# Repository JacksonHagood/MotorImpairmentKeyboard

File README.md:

# MotorImpairmentKeyboard

# MIKey

Members:
- Jackson Hagood
- Andrew Imwalle
- Brittany Jenkins
- Connie Liu
- Abhishek More
- Max Smith

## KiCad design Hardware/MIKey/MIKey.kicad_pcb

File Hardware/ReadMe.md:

# Hardware

Gerber files for the footprint test, the matrix test, and the final Gerber files for the PCB request

Designing PCB

1. Follow install instructions at https://github.com/ncarandini/KiCad-RP-Pico to get the Raspberry Pi Pico footprint installed in KiCad
2. Ensure the Gateron Slim Footprint is also installed in KiCad
3. Use https://www.pcbway.com/blog/PCB_Design_Tutorial/How_to_Export_Gerber_and_Production_Files_in_KiCad.html to export files from KiCad to Gerber files used for printing PCB

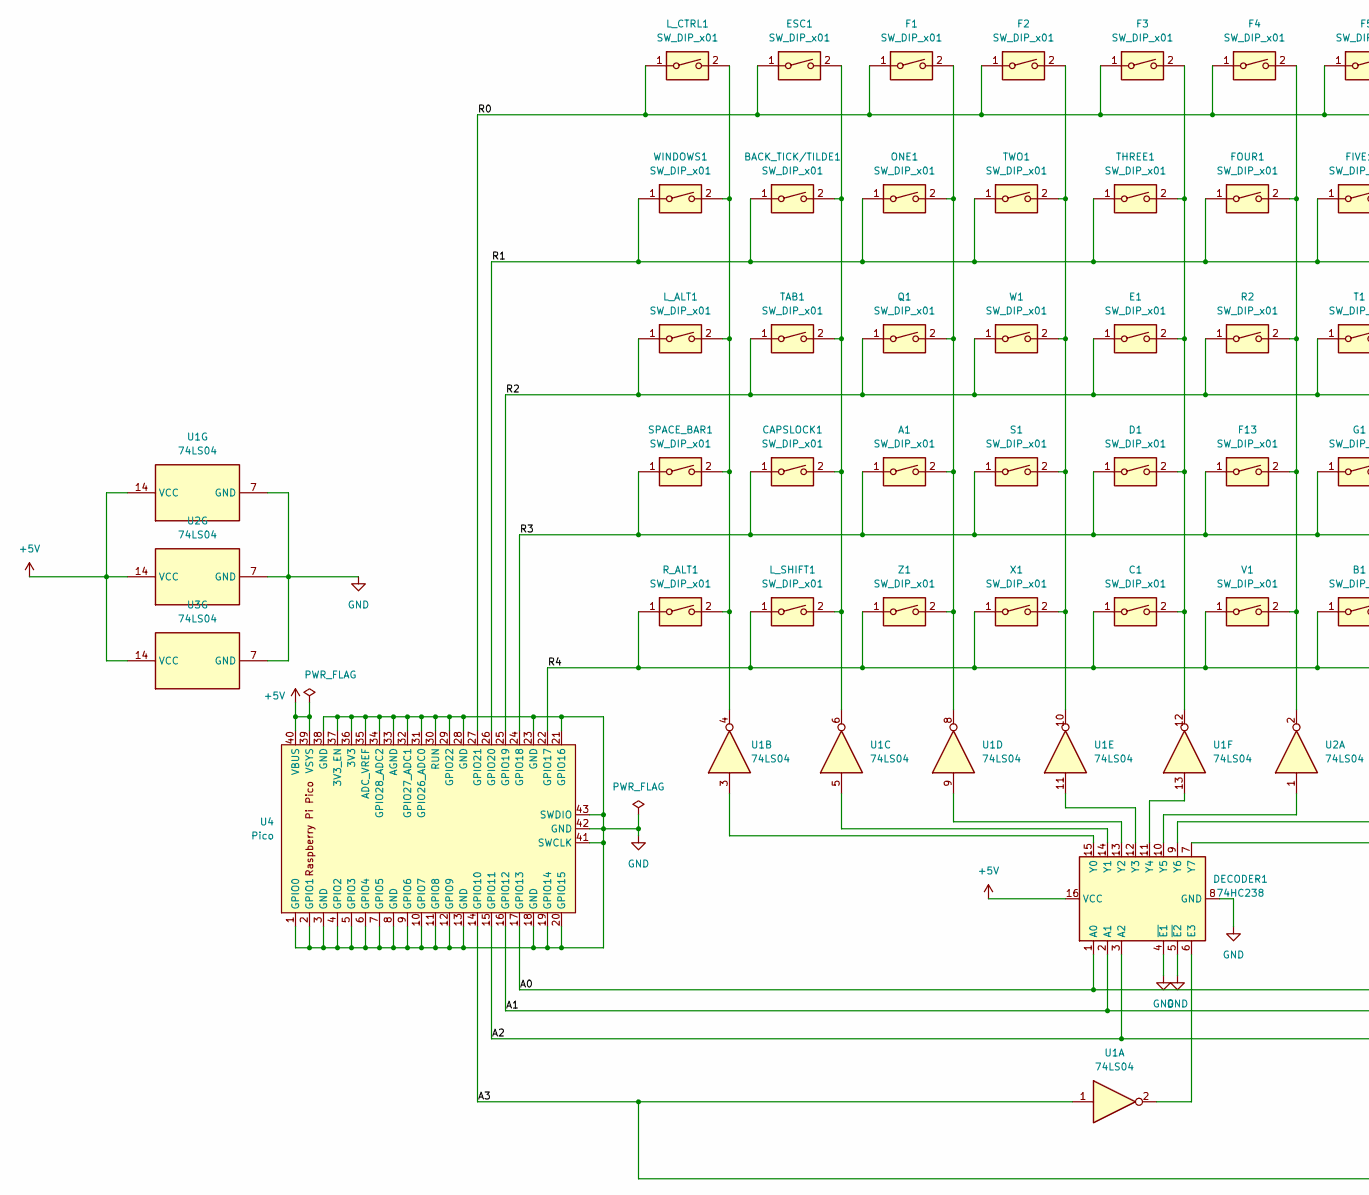
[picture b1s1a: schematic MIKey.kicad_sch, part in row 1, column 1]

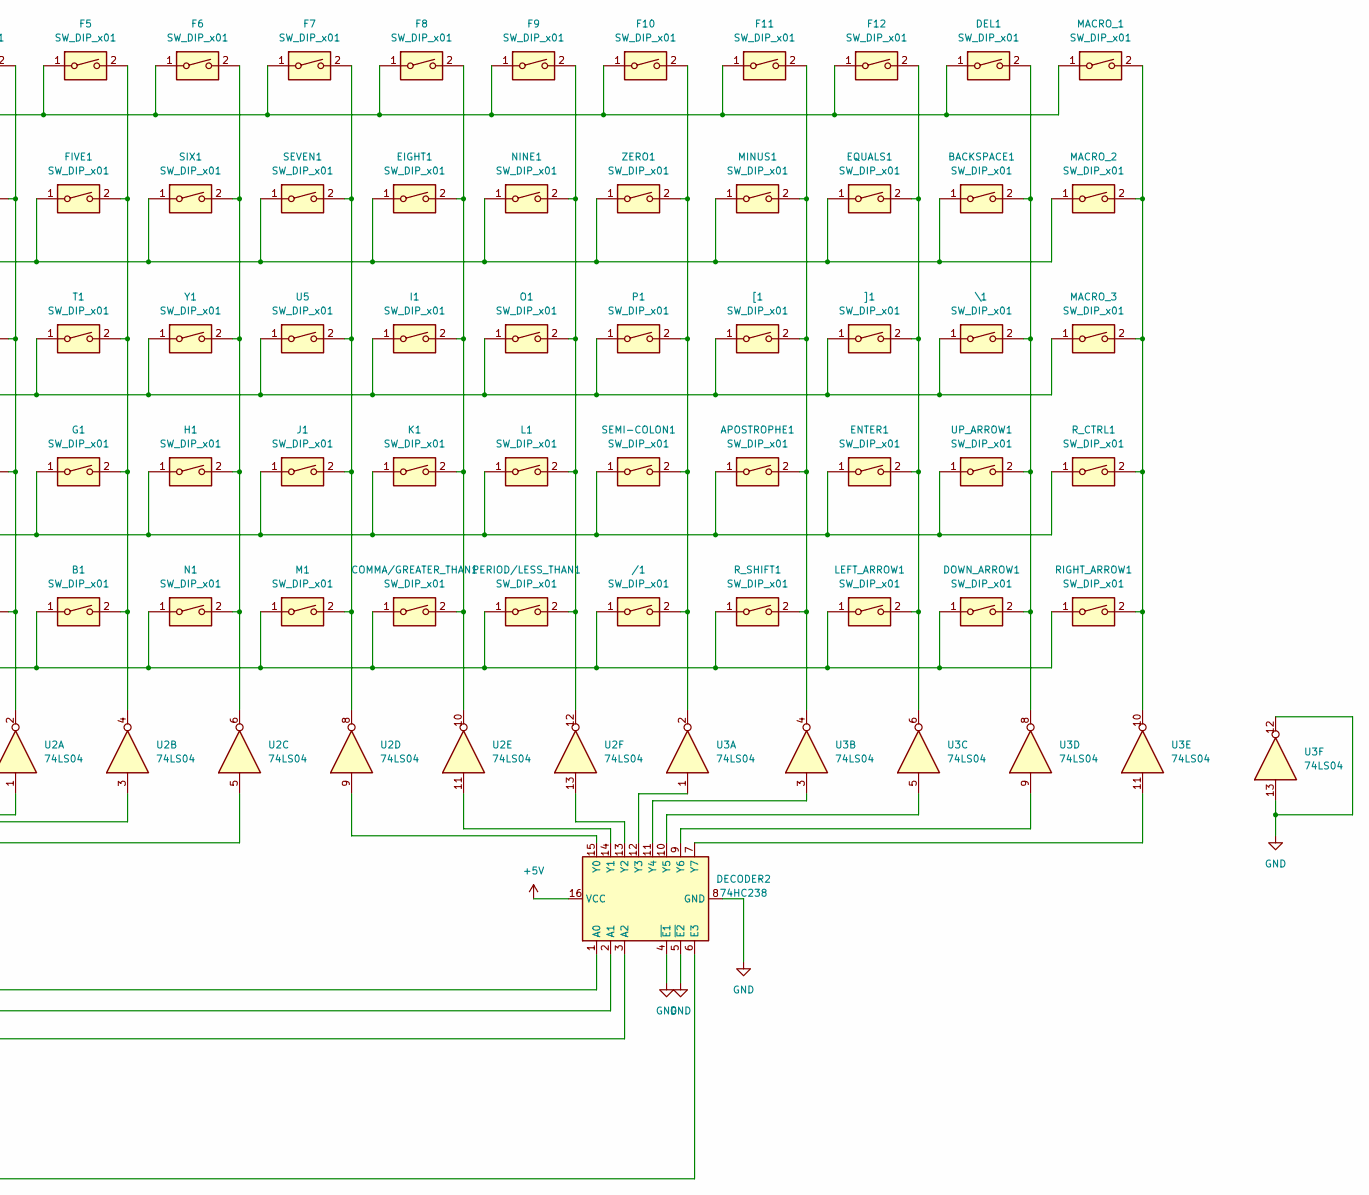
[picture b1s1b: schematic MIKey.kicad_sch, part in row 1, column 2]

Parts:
/1: SW_DIP_x01; gateron_slim
A1: SW_DIP_x01; gateron_slim
APOSTROPHE1: SW_DIP_x01; gateron_slim
B1: SW_DIP_x01; gateron_slim
BACKSPACE1: SW_DIP_x01; gateron_slim
BACK_TICK/TILDE1: SW_DIP_x01; gateron_slim
C1: SW_DIP_x01; gateron_slim
CAPSLOCK1: SW_DIP_x01; gateron_slim
COMMA/GREATER_THAN1: SW_DIP_x01; gateron_slim
D1: SW_DIP_x01; gateron_slim
DECODER1, DECODER2: 74HC238; DIP-16_W7.62mm
DEL1: SW_DIP_x01; gateron_slim
DOWN_ARROW1: SW_DIP_x01; gateron_slim
E1: SW_DIP_x01; gateron_slim
EIGHT1: SW_DIP_x01; gateron_slim
ENTER1: SW_DIP_x01; gateron_slim
EQUALS1: SW_DIP_x01; gateron_slim
ESC1: SW_DIP_x01; gateron_slim
F1, F2, F3, F4, F5, F6, F7, F8, F9, F10, F11, F12, F13: SW_DIP_x01; gateron_slim
FIVE1: SW_DIP_x01; gateron_slim
FOUR1: SW_DIP_x01; gateron_slim
G1: SW_DIP_x01; gateron_slim
H1: SW_DIP_x01; gateron_slim
I1: SW_DIP_x01; gateron_slim
J1: SW_DIP_x01; gateron_slim
K1: SW_DIP_x01; gateron_slim
L1: SW_DIP_x01; gateron_slim
LEFT_ARROW1: SW_DIP_x01; gateron_slim
L_ALT1: SW_DIP_x01; gateron_slim
L_CTRL1: SW_DIP_x01; gateron_slim
L_SHIFT1: SW_DIP_x01; gateron_slim
M1: SW_DIP_x01; gateron_slim
MACRO_1, MACRO_2, MACRO_3: SW_DIP_x01; gateron_slim
MINUS1: SW_DIP_x01; gateron_slim
N1: SW_DIP_x01; gateron_slim
NINE1: SW_DIP_x01; gateron_slim
O1: SW_DIP_x01; gateron_slim
ONE1: SW_DIP_x01; gateron_slim
P1: SW_DIP_x01; gateron_slim
PERIOD/LESS_THAN1: SW_DIP_x01; gateron_slim
Q1: SW_DIP_x01; gateron_slim
R2: SW_DIP_x01; gateron_slim
RIGHT_ARROW1: SW_DIP_x01; gateron_slim
R_ALT1: SW_DIP_x01; gateron_slim
R_CTRL1: SW_DIP_x01; gateron_slim
R_SHIFT1: SW_DIP_x01; gateron_slim
S1: SW_DIP_x01; gateron_slim
SEMI-COLON1: SW_DIP_x01; gateron_slim
SEVEN1: SW_DIP_x01; gateron_slim
SIX1: SW_DIP_x01; gateron_slim
SPACE_BAR1: SW_DIP_x01; gateron_slim
T1: SW_DIP_x01; gateron_slim
TAB1: SW_DIP_x01; gateron_slim
THREE1: SW_DIP_x01; gateron_slim
TWO1: SW_DIP_x01; gateron_slim
U1, U2, U3: 74LS04; DIP-14_W7.62mm
U4: Pico; RPi_Pico_SMD_TH
U5: SW_DIP_x01; gateron_slim
UP_ARROW1: SW_DIP_x01; gateron_slim
V1: SW_DIP_x01; gateron_slim
W1: SW_DIP_x01; gateron_slim
WINDOWS1: SW_DIP_x01; gateron_slim
X1: SW_DIP_x01; gateron_slim
Y1: SW_DIP_x01; gateron_slim
Z1: SW_DIP_x01; gateron_slim
ZERO1: SW_DIP_x01; gateron_slim
[1: SW_DIP_x01; gateron_slim
\1: SW_DIP_x01; gateron_slim
]1: SW_DIP_x01; gateron_slim

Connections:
+5V: DECODER1.16 (VCC), DECODER2.16 (VCC), U1.14 (VCC), U2.14 (VCC), U3.14 (VCC), U4.39 (VSYS), U4.40 (VBUS)
/A0: DECODER1.1 (A0), DECODER2.1 (A0), U4.17 (GPIO13)
/A1: DECODER1.2 (A1), DECODER2.2 (A1), U4.16 (GPIO12)
/A2: DECODER1.3 (A2), DECODER2.3 (A2), U4.15 (GPIO11)
/A3: DECODER2.6 (E3), U1.1, U4.14 (GPIO10)
/R0: DEL1.1, ESC1.1, F1.1, F2.1, F3.1, F4.1, F5.1, F6.1, F7.1, F8.1, F9.1, F10.1, F11.1, F12.1, L_CTRL1.1, MACRO_1.1, U4.27 (GPIO21)
/R1: BACKSPACE1.1, BACK_TICK/TILDE1.1, EIGHT1.1, EQUALS1.1, FIVE1.1, FOUR1.1, MACRO_2.1, MINUS1.1, NINE1.1, ONE1.1, SEVEN1.1, SIX1.1, THREE1.1, TWO1.1, U4.26 (GPIO20), WINDOWS1.1, ZERO1.1
/R2: E1.1, I1.1, L_ALT1.1, MACRO_3.1, O1.1, P1.1, Q1.1, R2.1, T1.1, TAB1.1, U4.25 (GPIO19), U5.1, W1.1, Y1.1, [1.1, \1.1, ]1.1
/R3: A1.1, APOSTROPHE1.1, CAPSLOCK1.1, D1.1, ENTER1.1, F13.1, G1.1, H1.1, J1.1, K1.1, L1.1, R_CTRL1.1, S1.1, SEMI-COLON1.1, SPACE_BAR1.1, U4.24 (GPIO18), UP_ARROW1.1
/R4: /1.1, B1.1, C1.1, COMMA/GREATER_THAN1.1, DOWN_ARROW1.1, LEFT_ARROW1.1, L_SHIFT1.1, M1.1, N1.1, PERIOD/LESS_THAN1.1, RIGHT_ARROW1.1, R_ALT1.1, R_SHIFT1.1, U4.22 (GPIO17), V1.1, X1.1, Z1.1; also elsewhere on the board
GND: DECODER1.4 (~E1), DECODER1.5 (~E2), DECODER1.8 (GND), DECODER2.4 (~E1), DECODER2.5 (~E2), DECODER2.8 (GND), U1.7 (GND), U2.7 (GND), U3.7 (GND), U3.12, U3.13, U4.1 (GPIO0), U4.2 (GPIO1), U4.3 (GND), U4.4 (GPIO2), U4.5 (GPIO3), U4.6 (GPIO4), U4.7 (GPIO5), U4.8 (GND), U4.9 (GPIO6), U4.10 (GPIO7), U4.11 (GPIO8), U4.12 (GPIO9), U4.13 (GND), U4.18 (GND), U4.19 (GPIO14), U4.20 (GPIO15), U4.21 (GPIO16), U4.23 (GND), U4.28 (GND), U4.29 (GPIO22), U4.30 (RUN), U4.31 (GPIO26_ADC0), U4.32 (GPIO27_ADC1), U4.33 (AGND), U4.34 (GPIO28_ADC2), U4.35 (ADC_VREF), U4.36 (3V3), U4.37 (3V3_EN), U4.38 (GND), U4.41 (SWCLK), U4.42 (GND), U4.43 (SWDIO)
unnamed: /1.2, F10.2, P1.2, SEMI-COLON1.2, U3.2, ZERO1.2
unnamed: A1.2, F1.2, ONE1.2, Q1.2, U1.8, Z1.2
unnamed: APOSTROPHE1.2, F11.2, MINUS1.2, R_SHIFT1.2, U3.4, [1.2
unnamed: B1.2, F5.2, FIVE1.2, G1.2, T1.2, U2.4
unnamed: BACKSPACE1.2, DEL1.2, DOWN_ARROW1.2, U3.8, UP_ARROW1.2, \1.2
unnamed: BACK_TICK/TILDE1.2, CAPSLOCK1.2, ESC1.2, L_SHIFT1.2, TAB1.2, U1.6
unnamed: C1.2, D1.2, E1.2, F3.2, THREE1.2, U1.12
unnamed 18: COMMA/GREATER_THAN1.2, EIGHT1.2, F8.2, I1.2, K1.2, U2.10; also elsewhere on the board
unnamed: DECODER1.6 (E3), U1.2
unnamed: DECODER1.7 (Y7), U2.5
unnamed: DECODER1.9 (Y6), U2.3
unnamed: DECODER1.10 (Y5), U2.1
unnamed: DECODER1.11 (Y4), U1.13
unnamed: DECODER1.12 (Y3), U1.11
unnamed: DECODER1.13 (Y2), U1.9
unnamed: DECODER1.14 (Y1), U1.5
unnamed: DECODER1.15 (Y0), U1.3
unnamed: DECODER2.7 (Y7), U3.11
unnamed: DECODER2.9 (Y6), U3.9
unnamed: DECODER2.10 (Y5), U3.5
unnamed: DECODER2.11 (Y4), U3.3
unnamed: DECODER2.12 (Y3), U3.1
unnamed: DECODER2.13 (Y2), U2.13
unnamed: DECODER2.14 (Y1), U2.11
unnamed: DECODER2.15 (Y0), U2.9
unnamed: ENTER1.2, EQUALS1.2, F12.2, LEFT_ARROW1.2, U3.6, ]1.2
unnamed: F2.2, S1.2, TWO1.2, U1.10, W1.2, X1.2
unnamed: F6.2, H1.2, N1.2, SIX1.2, U2.6, Y1.2
unnamed: F7.2, J1.2, M1.2, SEVEN1.2, U2.8, U5.2
unnamed 40: F9.2, L1.2, NINE1.2, O1.2, PERIOD/LESS_THAN1.2, U2.12; also elsewhere on the board
unnamed: F4.2, F13.2, FOUR1.2, R2.2, U2.2, V1.2
unnamed: L_ALT1.2, L_CTRL1.2, R_ALT1.2, SPACE_BAR1.2, U1.4, WINDOWS1.2
unnamed: MACRO_1.2, MACRO_2.2, MACRO_3.2, RIGHT_ARROW1.2, R_CTRL1.2, U3.10

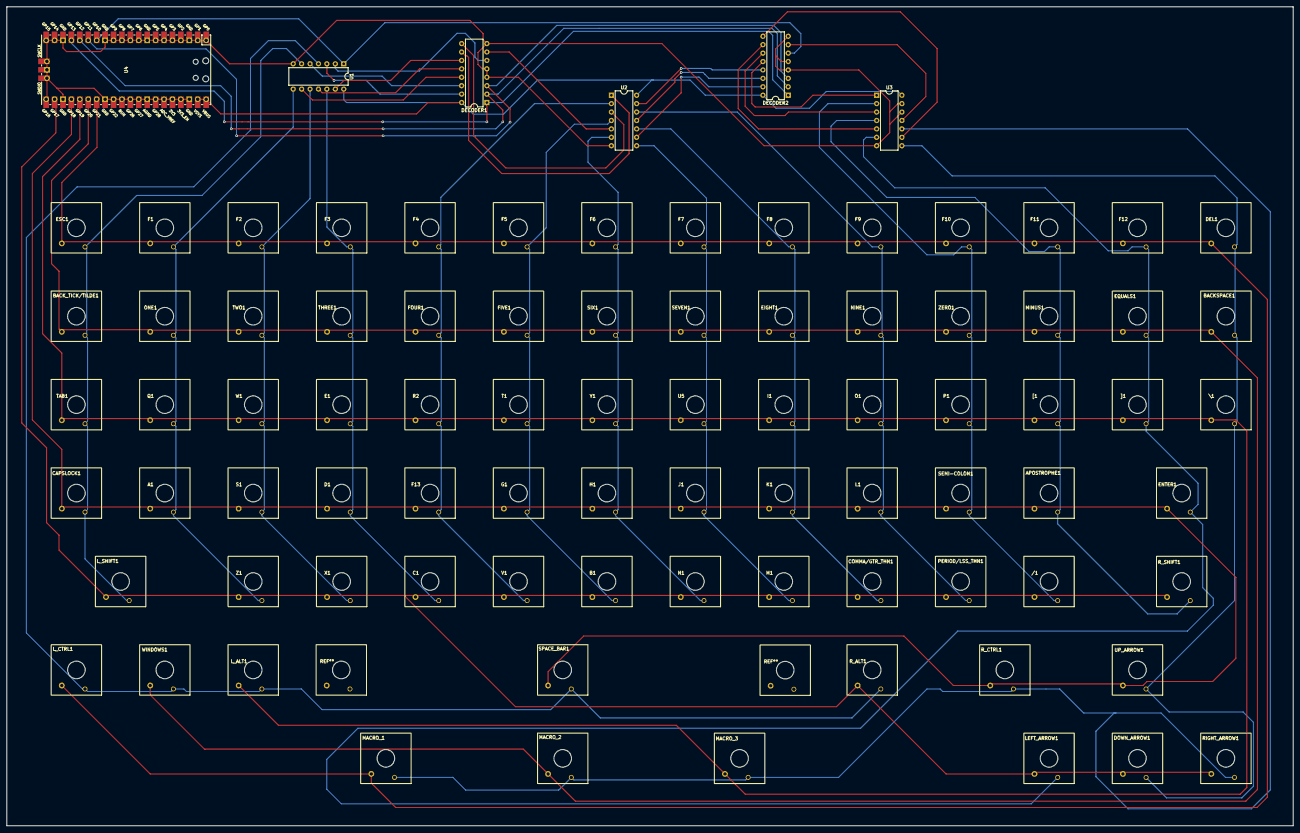
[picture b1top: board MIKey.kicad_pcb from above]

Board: 2 copper layers, 388.0 x 247.0 mm, 86 parts (0 on the bottom side), 44 nets.

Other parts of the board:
COMMA/GTR_THN1: SW_DIP_x01; gateron_slim
PERIOD/LSS_THN1: SW_DIP_x01; gateron_slim

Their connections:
/R4: COMMA/GTR_THN1.1, PERIOD/LSS_THN1.1; also elsewhere on the board
unnamed 18: COMMA/GTR_THN1.2; also elsewhere on the board
unnamed 40: PERIOD/LSS_THN1.2; also elsewhere on the board

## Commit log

2022-09-21 Node.h skeleton / initial code
2022-09-22 node documentation
2022-09-26 Trie skeleton code
2022-09-26 Design and Implement Software Algorithms: ReadMe Jackson Hagood
2022-09-26 MIK-8: MIKey
2022-09-26 MIK-47: Skeleton code
2022-09-26 MIK-47 Trie
2022-09-26 MIK-47 test
2022-09-26 MIK-47 test 2
2022-09-26 Trie constructor
2022-09-28 trie traversal autocomplete example from GeeksforGeeks
2022-09-28 getCandidates() start
2022-09-28 getCandidates() and test program
2022-09-28 getCandidates() fix
2022-10-03 Trie comments and improvements
2022-10-03 Small test file changes
2022-10-03 Directory Restructure
2022-10-03 ReadMe's
2022-10-03 adding the keycap stl
2022-10-03 MENA Protocol
2022-10-04 Key mapping
2022-10-13 flattened keycap top and changed slope to be flat
2022-10-15 Add key scanning skeleton
2022-10-18 Driver program stark, MakeFile, and documentation
2022-10-18 ReadMe typo
2022-10-18 ReadMe typo 2
2022-10-24 Sending keystrokes over USB functionality
2022-10-25 Cleaned up code
2022-11-02 added LCD
2022-11-21 Added key scanning software code.py
2022-11-28 merged
2022-11-28 Added pico code
2022-11-29 Restructure and cleanup
2022-11-29 Housing STL
2022-11-30 Documents
2022-11-30 renaming
2022-12-01 Added Housing and Keycap STL files
2022-12-01 Oops my bad. Moving modeling to modeling
2022-12-03 PCB Designs
2022-12-06 Added Notebook Folder
2022-12-06 Uploaded smith_max_notebook.pdf
2022-12-06 change notebook name
2022-12-06 Connie Notebook
2022-12-06 Final Report
2022-12-06 abhishek notebook
2022-12-06 Notebook & renaming
